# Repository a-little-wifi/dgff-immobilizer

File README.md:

# DGFF Immobilizer

A DGFF to PCIe adapter, based on my work on MXM Immobilizer (DGFF is just funny MXM)

Still extremely experimental and not anywhere near ready for use or testing  
DGFF pinouts taken from Dell Precision 7740 LA-H281P and Area51M LA-G881P boards  
The DGFF footprint's dimensions are unlikely to be accurate, it has been recreated from pixel measurements of a high-resolution image of a DGFF card. In any case they do not match the likely more accurate Framework Laptop 16"'s FXBeam footprint available elsewhere.  
This adapter is designed so far to work with Dell Precision and Alienware cards, their pinouts seem to be mostly identical but mirrored, so the Alienware one connects on the back side.  

I don't think I'll be finishing this project anytime soon, but maybe it can be a useful resource for others experimenting with DGFF

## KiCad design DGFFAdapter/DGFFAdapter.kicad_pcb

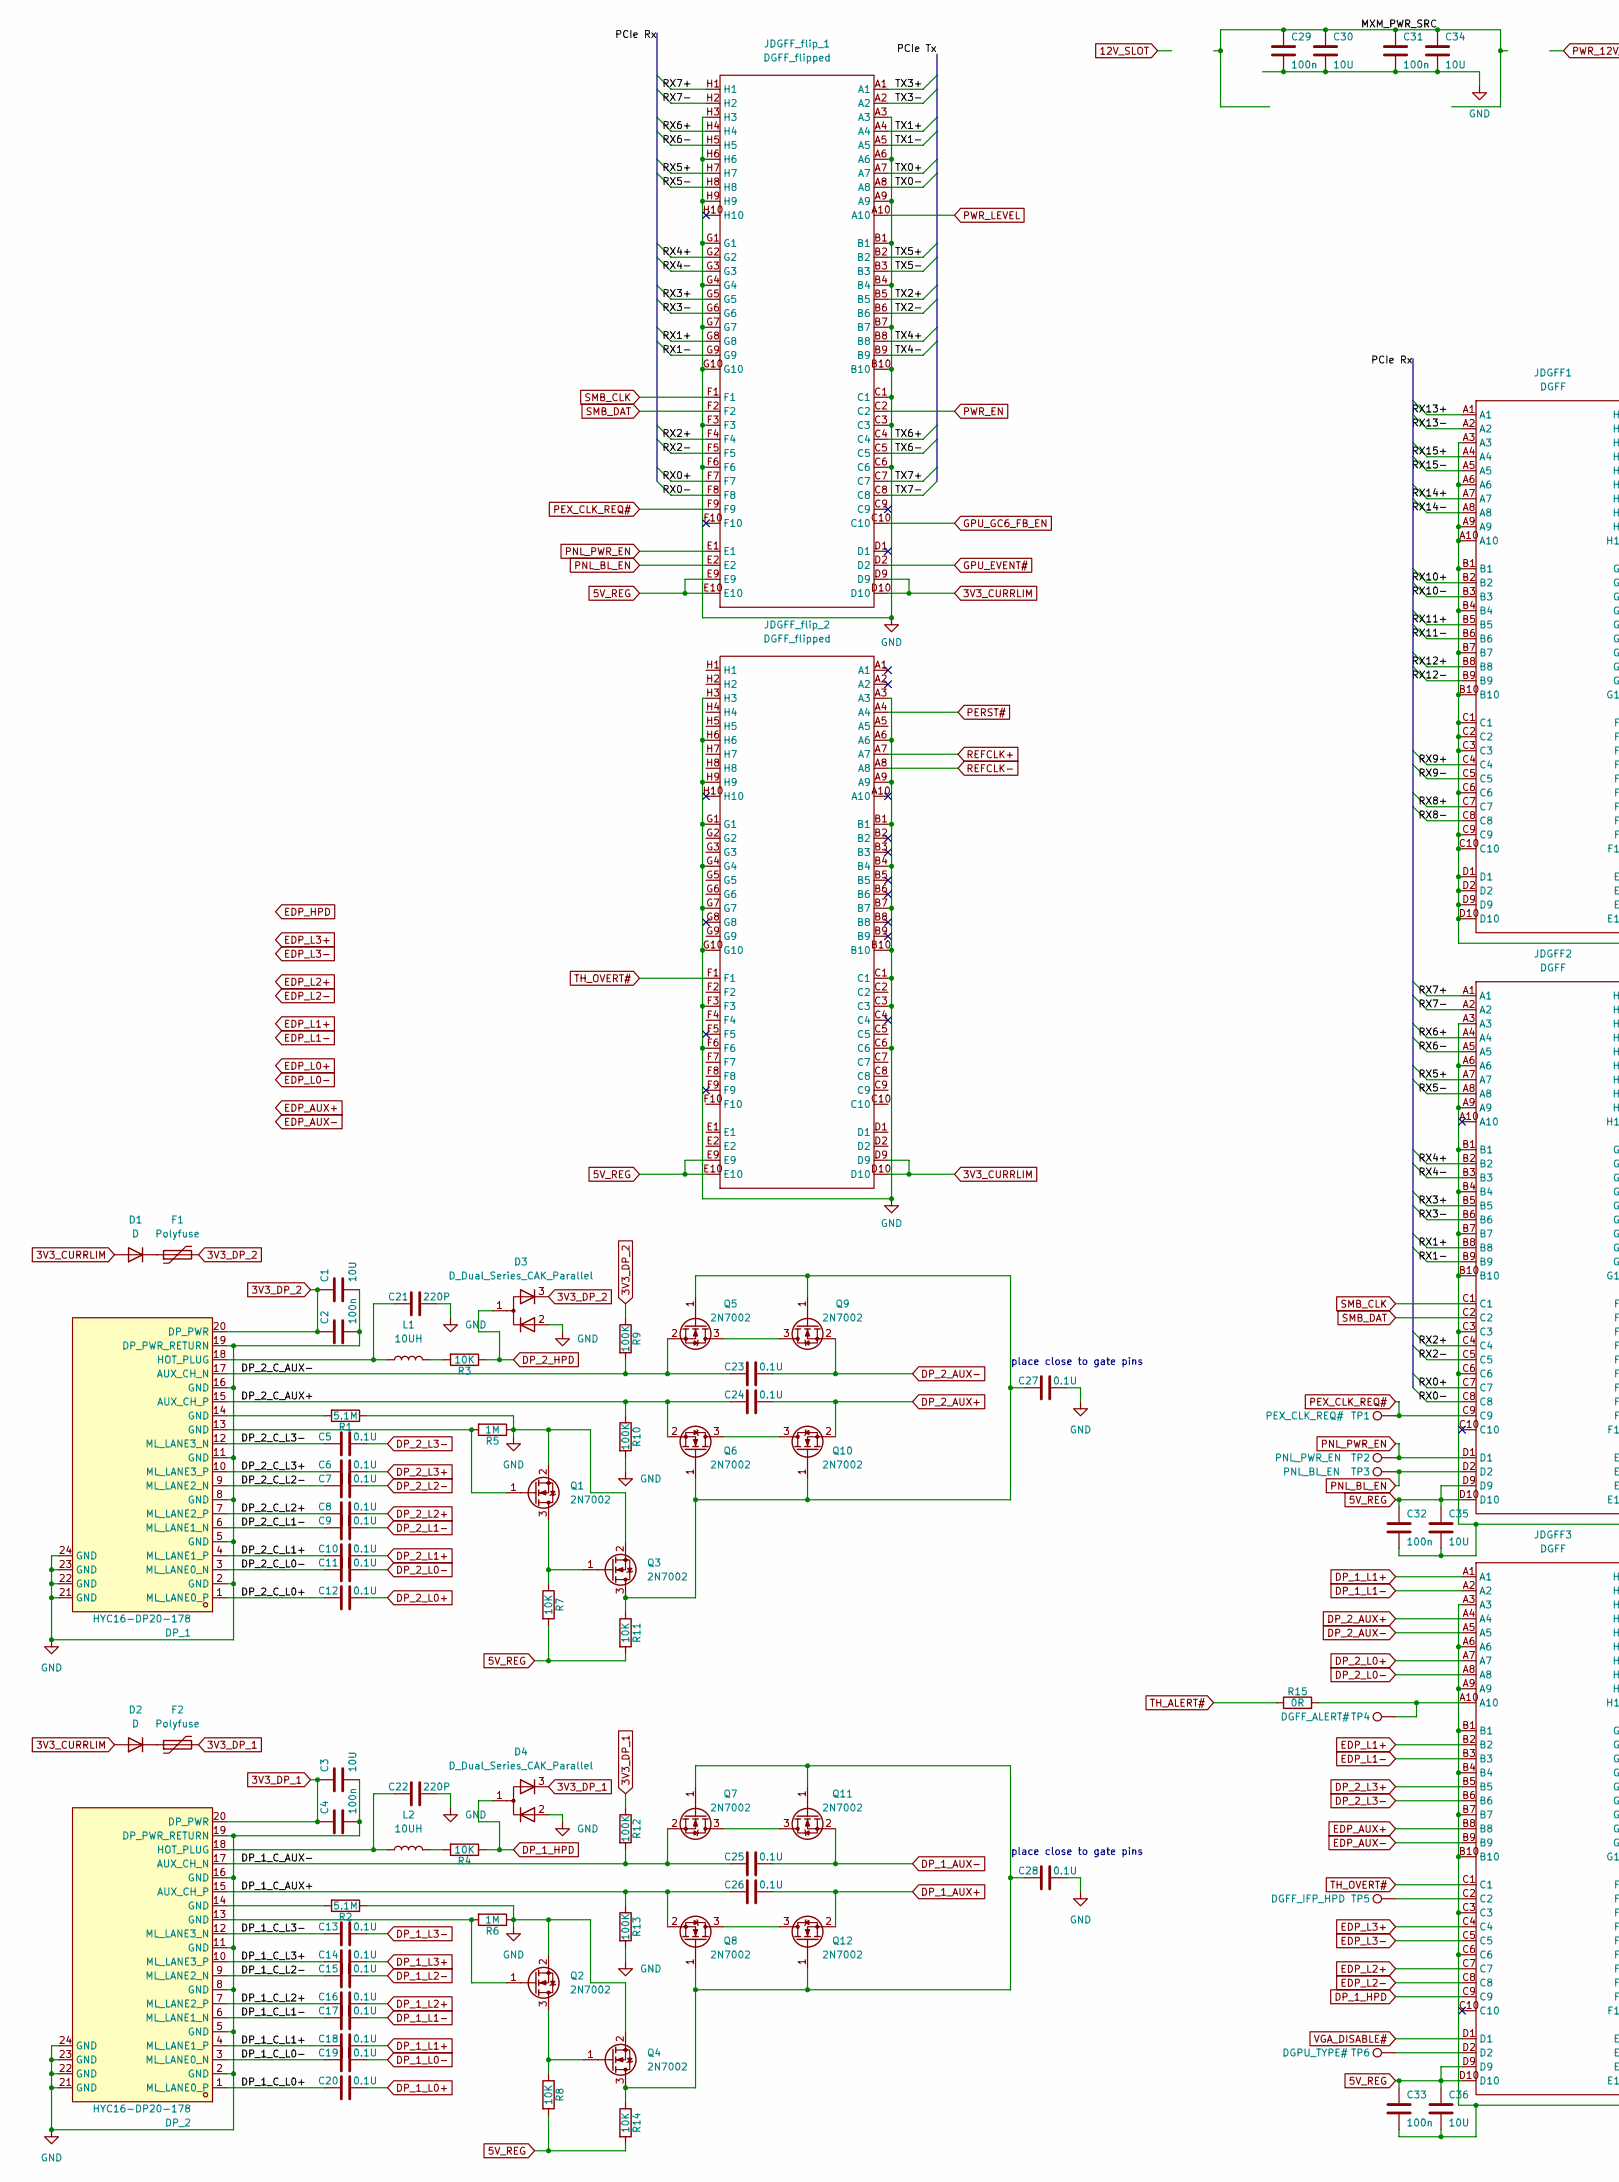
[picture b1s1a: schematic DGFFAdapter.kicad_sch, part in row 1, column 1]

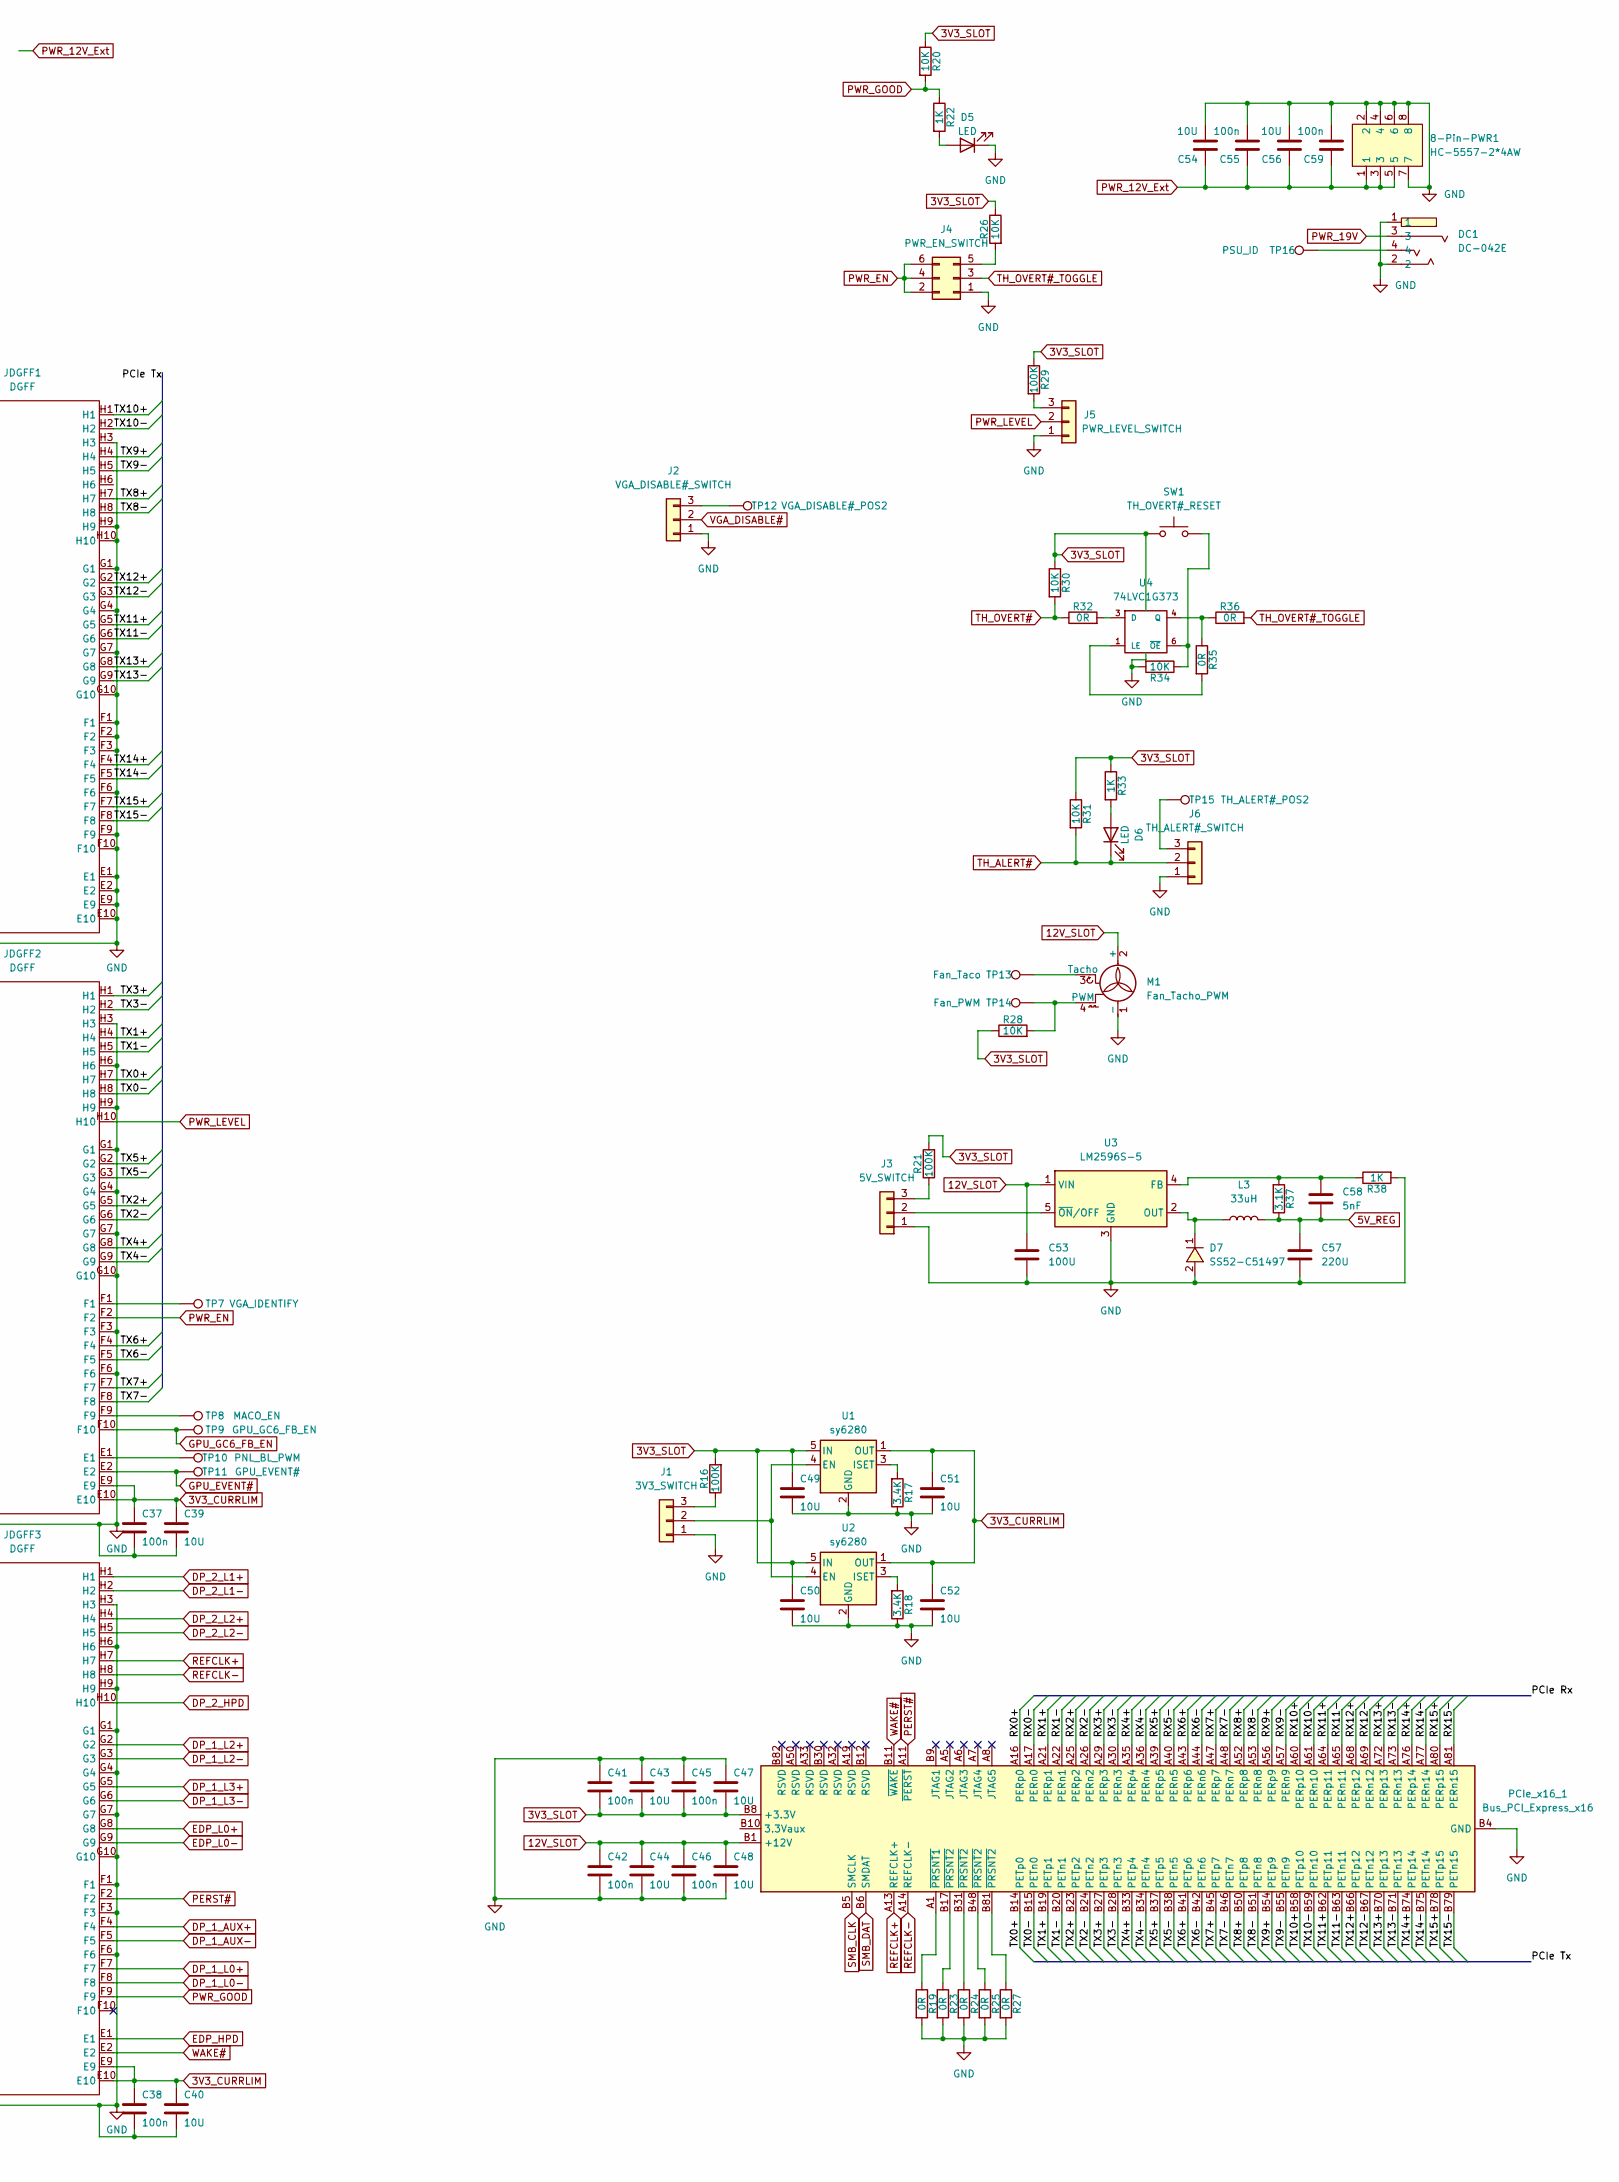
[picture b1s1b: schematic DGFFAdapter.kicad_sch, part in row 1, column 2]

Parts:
8-Pin-PWR1: HC-5557-2*4AW; CONN-TH_8P-P4.20_5557-2X4AW; LCSC Part C2845789
C1, C3, C30, C34, C35, C36, C39, C40, C43, C44, C47, C48, C49, C50, C51, C52, C54, C56: 10U; C_0603_1608Metric_Pad1.08x0.95mm_HandSolder
C2, C4, C29, C31, C32, C33, C37, C38, C41, C42, C45, C46, C55, C59: 100n; C_0603_1608Metric
C5, C6, C7, C8, C9, C10, C11, C12, C13, C14, C15, C16, C17, C18, C19, C20, C23, C24, C25, C26: 0.1U; C_0402_1005Metric
C21, C22: 220P; C_0603_1608Metric
C27, C28: 0.1U; C_0603_1608Metric
C53: 100U; C_Elec_6.3x7.7
C57: 220U; C_Elec_6.3x7.7
C58: 5nF; C_0603_1608Metric
D1, D2: D; D_SMA
D3, D4: D_Dual_Series_CAK_Parallel; SOT-23
D5, D6: LED; LED_0603_1608Metric
D7: SS52-C51497; SMB_L4.6-W3.6-LS5.3-RD; LCSC Part C51497
DC1: DC-042E; DC-IN-TH_DC-042E; LCSC Part C397340
DP_1, DP_2: HYC16-DP20-178; DP-SMD_HYC16-DP20-178; LCSC Part C711350
F1, F2: Polyfuse; Fuse_0805_2012Metric
J1: 3V3_SWITCH; PinHeader_1x03_P2.54mm_Vertical
J2: VGA_DISABLE#_SWITCH; PinHeader_1x03_P2.54mm_Vertical
J3: 5V_SWITCH; PinHeader_1x03_P2.54mm_Vertical
J4: PWR_EN_SWITCH; PinHeader_2x03_P2.54mm_Vertical
J5: PWR_LEVEL_SWITCH; PinHeader_1x03_P2.54mm_Vertical
J6: TH_ALERT#_SWITCH; PinHeader_1x03_P2.54mm_Vertical
JDGFF1, JDGFF2, JDGFF3: DGFF
JDGFF_flip_1, JDGFF_flip_2: DGFF_flipped; DGFF
L1, L2: 10UH; L_0603_1608Metric_Pad1.05x0.95mm_HandSolder
L3: 33uH; L_12x12mm_H8mm
M1: Fan_Tacho_PWM; FanPinHeader_1x04_P2.54mm_Vertical
PCIe_x16_1: Bus_PCI_Express_x16; BUS_PCIexpress_x16
Q1, Q2, Q3, Q4, Q5, Q6, Q7, Q8, Q9, Q10, Q11, Q12: 2N7002; SOT-23
R1, R2: 5.1M; R_0603_1608Metric
R3, R4, R7, R8, R11, R14, R20, R26, R28, R30, R31, R34: 10K; R_0603_1608Metric
R5, R6: 1M; R_0603_1608Metric
R9, R10, R12, R13, R16, R21, R29: 100K; R_0603_1608Metric
R15, R19, R23, R24, R25, R27, R32, R35, R36: 0R; R_0603_1608Metric
R17, R18: 3.4K; R_0603_1608Metric
R22, R33, R38: 1K; R_0603_1608Metric
R37: 3.1K; R_0603_1608Metric
SW1: TH_OVERT#_RESET; SW_SPST_EVQPE1
TP1: PEX_CLK_REQ#; PinHeader_1x01_P2.54mm_Vertical
TP2: PNL_PWR_EN; PinHeader_1x01_P2.54mm_Vertical
TP3: PNL_BL_EN; PinHeader_1x01_P2.54mm_Vertical
TP4: DGFF_ALERT#; PinHeader_1x01_P2.54mm_Vertical
TP5: DGFF_IFP_HPD; PinHeader_1x01_P2.54mm_Vertical
TP6: DGPU_TYPE#; PinHeader_1x01_P2.54mm_Vertical
TP7: VGA_IDENTIFY; PinHeader_1x01_P2.54mm_Vertical
TP8: MACO_EN; PinHeader_1x01_P2.54mm_Vertical
TP9: GPU_GC6_FB_EN; PinHeader_1x01_P2.54mm_Vertical
TP10: PNL_BL_PWM; PinHeader_1x01_P2.54mm_Vertical
TP11: GPU_EVENT#; PinHeader_1x01_P2.54mm_Vertical
TP12: VGA_DISABLE#_POS2; PinHeader_1x01_P2.54mm_Vertical
TP13: Fan_Taco; PinHeader_1x01_P2.54mm_Vertical
TP14: Fan_PWM; PinHeader_1x01_P2.54mm_Vertical
TP15: TH_ALERT#_POS2; PinHeader_1x01_P2.54mm_Vertical
TP16: PSU_ID; PinHeader_1x01_P2.54mm_Vertical
U1, U2: sy6280; SOT-23-5
U3: LM2596S-5; TO-263-5_TabPin3
U4: 74LVC1G373; SOT-23-6

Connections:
3V3_CURRLIM: C37.1, C38.1, C39.1, C40.1, C51.1, C52.1, D1.2 (A), D2.2 (A), JDGFF2.E9, JDGFF2.E10, JDGFF3.E9, JDGFF3.E10, JDGFF_flip_1.D9, JDGFF_flip_1.D10, JDGFF_flip_2.D9, JDGFF_flip_2.D10, U1.1 (OUT), U2.1 (OUT)
3V3_DP_1: C3.1, C4.1, D4.3 (K), DP_2.20 (DP_PWR), F2.2, R12.1
3V3_DP_2: C1.1, C2.1, D3.3 (K), DP_1.20 (DP_PWR), F1.2, R9.1
3V3_SLOT: C41.2, C43.2, C45.2, C47.2, C49.1, C50.1, PCIe_x16_1.A9 (+3.3V), PCIe_x16_1.A10 (+3.3V), PCIe_x16_1.B8 (+3.3V), R16.2, R20.1, R21.2, R26.1, R28.1, R29.1, R30.1, R31.1, R33.1, SW1.1, U1.5 (IN), U2.5 (IN), U4.5 (VCC)
5V_REG: C32.1, C33.1, C35.1, C36.1, C57.1, C58.2, JDGFF2.D9, JDGFF2.D10, JDGFF3.D9, JDGFF3.D10, JDGFF_flip_1.E9, JDGFF_flip_1.E10, JDGFF_flip_2.E9, JDGFF_flip_2.E10, L3.2, R7.2, R8.2, R11.2, R14.2, R37.1
12V_SLOT: C42.1, C44.1, C46.1, C48.1, C53.1, M1.2 (+), PCIe_x16_1.A2 (+12V), PCIe_x16_1.A3 (+12V), PCIe_x16_1.B1 (+12V), PCIe_x16_1.B2 (+12V), PCIe_x16_1.B3 (+12V), U3.1 (VIN)
/DP_1_C_AUX+: C26.2, DP_2.15 (AUX_CH_P), Q8.2 (S), R13.1
/DP_1_C_AUX-: C25.2, DP_2.17 (AUX_CH_N), Q7.2 (S), R12.2
/DP_1_C_L0+: C20.2, DP_2.1 (ML_LANE0_P)
/DP_1_C_L0-: C19.2, DP_2.3 (ML_LANE0_N)
/DP_1_C_L1+: C18.2, DP_2.4 (ML_LANE1_P)
/DP_1_C_L1-: C17.2, DP_2.6 (ML_LANE1_N)
/DP_1_C_L2+: C16.2, DP_2.7 (ML_LANE2_P)
/DP_1_C_L2-: C15.2, DP_2.9 (ML_LANE2_N)
/DP_1_C_L3+: C14.2, DP_2.10 (ML_LANE3_P)
/DP_1_C_L3-: C13.2, DP_2.12 (ML_LANE3_N)
/DP_2_C_AUX+: C24.2, DP_1.15 (AUX_CH_P), Q6.2 (S), R10.1
/DP_2_C_AUX-: C23.2, DP_1.17 (AUX_CH_N), Q5.2 (S), R9.2
/DP_2_C_L0+: C12.2, DP_1.1 (ML_LANE0_P)
/DP_2_C_L0-: C11.2, DP_1.3 (ML_LANE0_N)
/DP_2_C_L1+: C10.2, DP_1.4 (ML_LANE1_P)
/DP_2_C_L1-: C9.2, DP_1.6 (ML_LANE1_N)
/DP_2_C_L2+: C8.2, DP_1.7 (ML_LANE2_P)
/DP_2_C_L2-: C7.2, DP_1.9 (ML_LANE2_N)
/DP_2_C_L3+: C6.2, DP_1.10 (ML_LANE3_P)
/DP_2_C_L3-: C5.2, DP_1.12 (ML_LANE3_N)
/MXM_PWR_SRC: C29.1, C30.1, C31.1, C34.1
/RX0+: JDGFF2.C7, JDGFF_flip_1.F7, PCIe_x16_1.A16 (PERp0)
/RX0-: JDGFF2.C8, JDGFF_flip_1.F8, PCIe_x16_1.A17 (PERn0)
/RX1+: JDGFF2.B8, JDGFF_flip_1.G8, PCIe_x16_1.A21 (PERp1)
/RX1-: JDGFF2.B9, JDGFF_flip_1.G9, PCIe_x16_1.A22 (PERn1)
/RX2+: JDGFF2.C4, JDGFF_flip_1.F4, PCIe_x16_1.A25 (PERp2)
/RX2-: JDGFF2.C5, JDGFF_flip_1.F5, PCIe_x16_1.A26 (PERn2)
/RX3+: JDGFF2.B5, JDGFF_flip_1.G5, PCIe_x16_1.A29 (PERp3)
/RX3-: JDGFF2.B6, JDGFF_flip_1.G6, PCIe_x16_1.A30 (PERn3)
/RX4+: JDGFF2.B2, JDGFF_flip_1.G2, PCIe_x16_1.A35 (PERp4)
/RX4-: JDGFF2.B3, JDGFF_flip_1.G3, PCIe_x16_1.A36 (PERn4)
/RX5+: JDGFF2.A7, JDGFF_flip_1.H7, PCIe_x16_1.A39 (PERp5)
/RX5-: JDGFF2.A8, JDGFF_flip_1.H8, PCIe_x16_1.A40 (PERn5)
/RX6+: JDGFF2.A4, JDGFF_flip_1.H4, PCIe_x16_1.A43 (PERp6)
/RX6-: JDGFF2.A5, JDGFF_flip_1.H5, PCIe_x16_1.A44 (PERn6)
/RX7+: JDGFF2.A1, JDGFF_flip_1.H1, PCIe_x16_1.A47 (PERp7)
/RX7-: JDGFF2.A2, JDGFF_flip_1.H2, PCIe_x16_1.A48 (PERn7)
/RX8+: JDGFF1.C7, PCIe_x16_1.A52 (PERp8)
/RX8-: JDGFF1.C8, PCIe_x16_1.A53 (PERn8)
/RX9+: JDGFF1.C4, PCIe_x16_1.A56 (PERp9)
/RX9-: JDGFF1.C5, PCIe_x16_1.A57 (PERn9)
/RX10+: JDGFF1.B2, PCIe_x16_1.A60 (PERp10)
/RX10-: JDGFF1.B3, PCIe_x16_1.A61 (PERn10)
/RX11+: JDGFF1.B5, PCIe_x16_1.A64 (PERp11)
/RX11-: JDGFF1.B6, PCIe_x16_1.A65 (PERn11)
/RX12+: JDGFF1.B8, PCIe_x16_1.A68 (PERp12)
/RX12-: JDGFF1.B9, PCIe_x16_1.A69 (PERn12)
/RX13+: JDGFF1.A1, PCIe_x16_1.A72 (PERp13)
/RX13-: JDGFF1.A2, PCIe_x16_1.A73 (PERn13)
/RX14+: JDGFF1.A7, PCIe_x16_1.A76 (PERp14)
/RX14-: JDGFF1.A8, PCIe_x16_1.A77 (PERn14)
/RX15+: JDGFF1.A4, PCIe_x16_1.A80 (PERp15)
/RX15-: JDGFF1.A5, PCIe_x16_1.A81 (PERn15)
/TX0+: JDGFF2.H7, JDGFF_flip_1.A7, PCIe_x16_1.B14 (PETp0)
/TX0-: JDGFF2.H8, JDGFF_flip_1.A8, PCIe_x16_1.B15 (PETn0)
/TX1+: JDGFF2.H4, JDGFF_flip_1.A4, PCIe_x16_1.B19 (PETp1)
/TX1-: JDGFF2.H5, JDGFF_flip_1.A5, PCIe_x16_1.B20 (PETn1)
/TX2+: JDGFF2.G5, JDGFF_flip_1.B5, PCIe_x16_1.B23 (PETp2)
/TX2-: JDGFF2.G6, JDGFF_flip_1.B6, PCIe_x16_1.B24 (PETn2)
/TX3+: JDGFF2.H1, JDGFF_flip_1.A1, PCIe_x16_1.B27 (PETp3)
/TX3-: JDGFF2.H2, JDGFF_flip_1.A2, PCIe_x16_1.B28 (PETn3)
/TX4+: JDGFF2.G8, JDGFF_flip_1.B8, PCIe_x16_1.B33 (PETp4)
/TX4-: JDGFF2.G9, JDGFF_flip_1.B9, PCIe_x16_1.B34 (PETn4)
/TX5+: JDGFF2.G2, JDGFF_flip_1.B2, PCIe_x16_1.B37 (PETp5)
/TX5-: JDGFF2.G3, JDGFF_flip_1.B3, PCIe_x16_1.B38 (PETn5)
/TX6+: JDGFF2.F4, JDGFF_flip_1.C4, PCIe_x16_1.B41 (PETp6)
/TX6-: JDGFF2.F5, JDGFF_flip_1.C5, PCIe_x16_1.B42 (PETn6)
/TX7+: JDGFF2.F7, JDGFF_flip_1.C7, PCIe_x16_1.B45 (PETp7)
/TX7-: JDGFF2.F8, JDGFF_flip_1.C8, PCIe_x16_1.B46 (PETn7)
/TX8+: JDGFF1.H7, PCIe_x16_1.B50 (PETp8)
/TX8-: JDGFF1.H8, PCIe_x16_1.B51 (PETn8)
/TX9+: JDGFF1.H4, PCIe_x16_1.B54 (PETp9)
/TX9-: JDGFF1.H5, PCIe_x16_1.B55 (PETn9)
/TX10+: JDGFF1.H1, PCIe_x16_1.B58 (PETp10)
/TX10-: JDGFF1.H2, PCIe_x16_1.B59 (PETn10)
/TX11+: JDGFF1.G5, PCIe_x16_1.B62 (PETp11)
/TX11-: JDGFF1.G6, PCIe_x16_1.B63 (PETn11)
/TX12+: JDGFF1.G2, PCIe_x16_1.B66 (PETp12)
/TX12-: JDGFF1.G3, PCIe_x16_1.B67 (PETn12)
/TX13+: JDGFF1.G8, PCIe_x16_1.B70 (PETp13)
/TX13-: JDGFF1.G9, PCIe_x16_1.B71 (PETn13)
/TX14+: JDGFF1.F4, PCIe_x16_1.B74 (PETp14)
/TX14-: JDGFF1.F5, PCIe_x16_1.B75 (PETn14)
/TX15+: JDGFF1.F7, PCIe_x16_1.B78 (PETp15)
/TX15-: JDGFF1.F8, PCIe_x16_1.B79 (PETn15)
DP_1_AUX+: C26.1, JDGFF3.F4, Q12.2 (S)
DP_1_AUX-: C25.1, JDGFF3.F5, Q11.2 (S)
DP_1_HPD: D4.1 (A), JDGFF3.C9, R4.1
DP_1_L0+: C20.1, JDGFF3.F7
DP_1_L0-: C19.1, JDGFF3.F8
DP_1_L1+: C18.1, JDGFF3.A1
DP_1_L1-: C17.1, JDGFF3.A2
DP_1_L2+: C16.1, JDGFF3.G2
DP_1_L2-: C15.1, JDGFF3.G3
DP_1_L3+: C14.1, JDGFF3.G5
DP_1_L3-: C13.1, JDGFF3.G6
DP_2_AUX+: C24.1, JDGFF3.A4, Q10.2 (S)
DP_2_AUX-: C23.1, JDGFF3.A5, Q9.2 (S)
DP_2_HPD: D3.1 (A), JDGFF3.H10, R3.1
DP_2_L0+: C12.1, JDGFF3.A7
DP_2_L0-: C11.1, JDGFF3.A8
DP_2_L1+: C10.1, JDGFF3.H1
DP_2_L1-: C9.1, JDGFF3.H2
DP_2_L2+: C8.1, JDGFF3.H4
DP_2_L2-: C7.1, JDGFF3.H5
DP_2_L3+: C6.1, JDGFF3.B5
DP_2_L3-: C5.1, JDGFF3.B6
EDP_AUX+: JDGFF3.B8
EDP_AUX-: JDGFF3.B9
EDP_HPD: JDGFF3.E1
EDP_L0+: JDGFF3.G8
EDP_L0-: JDGFF3.G9
EDP_L1+: JDGFF3.B2
EDP_L1-: JDGFF3.B3
EDP_L2+: JDGFF3.C7
EDP_L2-: JDGFF3.C8
EDP_L3+: JDGFF3.C4
EDP_L3-: JDGFF3.C5
GND: 8-Pin-PWR1.2, 8-Pin-PWR1.4, 8-Pin-PWR1.6, 8-Pin-PWR1.7, 8-Pin-PWR1.8, C1.2, C2.2, C3.2, C4.2, C21.1, C22.1, C27.1, C28.1, C29.2, C30.2, C31.2, C32.2, C33.2, C34.2, C35.2, C36.2, C37.2, C38.2, C39.2, C40.2, C41.1, C42.2, C43.1, C44.2, C45.1, C46.2, C47.1, C48.2, C49.2, C50.2, C51.2, C52.2, C53.2, C54.2, C55.2, C56.2, C57.2, C59.2, D3.2 (K), D4.2 (K), D5.1 (K), D7.2 (A), DC1.1, DC1.2, DP_1.2 (GND), DP_1.5 (GND), DP_1.8 (GND), DP_1.11 (GND), DP_1.16 (GND), DP_1.19 (DP_PWR_RETURN), DP_1.21 (GND), DP_1.22 (GND), DP_1.23 (GND), DP_1.24 (GND), DP_2.2 (GND), DP_2.5 (GND), DP_2.8 (GND), DP_2.11 (GND), DP_2.16 (GND), DP_2.19 (DP_PWR_RETURN), DP_2.21 (GND), DP_2.22 (GND), DP_2.23 (GND), DP_2.24 (GND), J1.1, J2.1, J3.1, J4.1, J5.1, J6.1, JDGFF1.A3, JDGFF1.A6, JDGFF1.A9, JDGFF1.A10, JDGFF1.B1, JDGFF1.B4, JDGFF1.B7, JDGFF1.B10, JDGFF1.C1, JDGFF1.C2, JDGFF1.C3, JDGFF1.C6, JDGFF1.C9, JDGFF1.C10, JDGFF1.D1, JDGFF1.D2, JDGFF1.D9, JDGFF1.D10, JDGFF1.E1, JDGFF1.E2, JDGFF1.E9, JDGFF1.E10, JDGFF1.F1, JDGFF1.F2, JDGFF1.F3, JDGFF1.F6, JDGFF1.F9, JDGFF1.F10, JDGFF1.G1, JDGFF1.G4, JDGFF1.G7, JDGFF1.G10, JDGFF1.H3, JDGFF1.H9, JDGFF1.H10, JDGFF2.A3, JDGFF2.A6, JDGFF2.A9, JDGFF2.B1, JDGFF2.B4, JDGFF2.B7, JDGFF2.B10, JDGFF2.C3, JDGFF2.C6, JDGFF2.F3, JDGFF2.F6, JDGFF2.G1, JDGFF2.G4, JDGFF2.G7, JDGFF2.G10, JDGFF2.H3, JDGFF2.H6, JDGFF2.H9, JDGFF3.A3, JDGFF3.A6, JDGFF3.A9, JDGFF3.B1, JDGFF3.B4, JDGFF3.B7, JDGFF3.B10, JDGFF3.C3, JDGFF3.C6, JDGFF3.F1, JDGFF3.F3, JDGFF3.F6, JDGFF3.G1, JDGFF3.G4, JDGFF3.G7, JDGFF3.G10, JDGFF3.H3, JDGFF3.H6, JDGFF3.H9, JDGFF_flip_1.A3, JDGFF_flip_1.A6, JDGFF_flip_1.A9, JDGFF_flip_1.B1, JDGFF_flip_1.B4, JDGFF_flip_1.B7, JDGFF_flip_1.B10, JDGFF_flip_1.C1, JDGFF_flip_1.C3, JDGFF_flip_1.C6, JDGFF_flip_1.F3, JDGFF_flip_1.F6, JDGFF_flip_1.G1, JDGFF_flip_1.G4, JDGFF_flip_1.G7, JDGFF_flip_1.G10, JDGFF_flip_1.H3, JDGFF_flip_1.H6, JDGFF_flip_1.H9, JDGFF_flip_2.A3, JDGFF_flip_2.A6, JDGFF_flip_2.A9, JDGFF_flip_2.B1, JDGFF_flip_2.B4, JDGFF_flip_2.B7, JDGFF_flip_2.B10, JDGFF_flip_2.C1, JDGFF_flip_2.C3, JDGFF_flip_2.C6, JDGFF_flip_2.F3, JDGFF_flip_2.F6, JDGFF_flip_2.G1, JDGFF_flip_2.G4, JDGFF_flip_2.G7, JDGFF_flip_2.G10, JDGFF_flip_2.H3, JDGFF_flip_2.H6, JDGFF_flip_2.H9, M1.1 (-), PCIe_x16_1.A4 (GND), PCIe_x16_1.A12 (GND), PCIe_x16_1.A15 (GND), PCIe_x16_1.A18 (GND), PCIe_x16_1.A20 (GND), PCIe_x16_1.A23 (GND), PCIe_x16_1.A24 (GND), PCIe_x16_1.A27 (GND), PCIe_x16_1.A28 (GND), PCIe_x16_1.A31 (GND), PCIe_x16_1.A34 (GND), PCIe_x16_1.A37 (GND), PCIe_x16_1.A38 (GND), PCIe_x16_1.A41 (GND), PCIe_x16_1.A42 (GND), PCIe_x16_1.A45 (GND), PCIe_x16_1.A46 (GND), PCIe_x16_1.A49 (GND), PCIe_x16_1.A51 (GND), PCIe_x16_1.A54 (GND), PCIe_x16_1.A55 (GND), PCIe_x16_1.A58 (GND), PCIe_x16_1.A59 (GND), PCIe_x16_1.A62 (GND), PCIe_x16_1.A63 (GND), PCIe_x16_1.A66 (GND), PCIe_x16_1.A67 (GND), PCIe_x16_1.A70 (GND), PCIe_x16_1.A71 (GND), PCIe_x16_1.A74 (GND), PCIe_x16_1.A75 (GND), PCIe_x16_1.A78 (GND), PCIe_x16_1.A79 (GND), PCIe_x16_1.A82 (GND), PCIe_x16_1.B4 (GND), PCIe_x16_1.B7 (GND), PCIe_x16_1.B13 (GND), PCIe_x16_1.B16 (GND), PCIe_x16_1.B18 (GND), PCIe_x16_1.B21 (GND), PCIe_x16_1.B22 (GND), PCIe_x16_1.B25 (GND), PCIe_x16_1.B26 (GND), PCIe_x16_1.B29 (GND), PCIe_x16_1.B32 (GND), PCIe_x16_1.B35 (GND), PCIe_x16_1.B36 (GND), PCIe_x16_1.B39 (GND), PCIe_x16_1.B40 (GND), PCIe_x16_1.B43 (GND), PCIe_x16_1.B44 (GND), PCIe_x16_1.B47 (GND), PCIe_x16_1.B49 (GND), PCIe_x16_1.B52 (GND), PCIe_x16_1.B53 (GND), PCIe_x16_1.B56 (GND), PCIe_x16_1.B57 (GND), PCIe_x16_1.B60 (GND), PCIe_x16_1.B61 (GND), PCIe_x16_1.B64 (GND), PCIe_x16_1.B65 (GND), PCIe_x16_1.B68 (GND), PCIe_x16_1.B69 (GND), PCIe_x16_1.B72 (GND), PCIe_x16_1.B73 (GND), PCIe_x16_1.B76 (GND), PCIe_x16_1.B77 (GND), PCIe_x16_1.B80 (GND), Q1.2 (S), Q2.2 (S), Q3.2 (S), Q4.2 (S), R1.1, R2.1, R5.1, R6.1, R10.2, R13.2, R17.1, R18.1, R19.2, R23.2, R24.2, R25.2, R27.2, R34.2, R38.2, U1.2 (GND), U2.2 (GND), U3.3 (GND), U4.2 (GND)
GPU_EVENT#: JDGFF2.E2, JDGFF_flip_1.D2, TP11.1
GPU_GC6_FB_EN: JDGFF2.F10, JDGFF_flip_1.C10, TP9.1
unnamed: D1.1 (K), F1.1
unnamed: D2.1 (K), F2.1
unnamed: D5.2 (A), R22.2
unnamed: D6.2 (A), R33.2
unnamed: D7.1 (C), L3.1, U3.2 (OUT)
unnamed: DC1.4, TP16.1
unnamed: DP_1.14 (GND), R1.2
unnamed: C21.2, DP_1.18 (HOT_PLUG), L1.1
unnamed: DP_2.14 (GND), R2.2
unnamed: C22.2, DP_2.18 (HOT_PLUG), L2.1
unnamed: J1.2, U1.4 (EN), U2.4 (EN)
unnamed: J1.3, R16.1
unnamed: J2.3, TP12.1
unnamed: J3.2, U3.5 (~ON/OFF)
unnamed: J3.3, R21.1
unnamed: J4.5, R26.2
unnamed: J5.3, R29.2
unnamed: J6.3, TP15.1
unnamed: JDGFF2.E1, TP10.1
unnamed: JDGFF2.F1, TP7.1
unnamed: JDGFF2.F9, TP8.1
unnamed: JDGFF3.A10, R15.2, TP4.1
unnamed: JDGFF3.C2, TP5.1
unnamed: JDGFF3.D2, TP6.1
unnamed: L1.2, R3.2
unnamed: L2.2, R4.2
unnamed: M1.4 (PWM), R28.2, TP14.1
unnamed: M1.3 (Tacho), TP13.1
unnamed: PCIe_x16_1.A1 (~PRSNT1), R19.1
unnamed: PCIe_x16_1.B17 (~PRSNT2), R23.1
unnamed: PCIe_x16_1.B31 (~PRSNT2), R24.1
unnamed: PCIe_x16_1.B48 (~PRSNT2), R25.1
unnamed: PCIe_x16_1.B81 (~PRSNT2), R27.1
unnamed: Q1.3 (D), Q3.1 (G), R7.1
unnamed: DP_1.13 (GND), Q1.1 (G), R5.2
unnamed: Q2.3 (D), Q4.1 (G), R8.1
unnamed: DP_2.13 (GND), Q2.1 (G), R6.2
unnamed: Q5.3 (D), Q9.3 (D)
unnamed: Q6.3 (D), Q10.3 (D)
unnamed: C27.2, Q3.3 (D), Q5.1 (G), Q6.1 (G), Q9.1 (G), Q10.1 (G), R11.1
unnamed: Q7.3 (D), Q11.3 (D)
unnamed: C28.2, Q4.3 (D), Q7.1 (G), Q8.1 (G), Q11.1 (G), Q12.1 (G), R14.1
unnamed: Q8.3 (D), Q12.3 (D)
unnamed: R17.2, U1.3 (ISET)
unnamed: R18.2, U2.3 (ISET)
unnamed: C58.1, R37.2, R38.1, U3.4 (FB)
unnamed: R32.2, U4.3 (D)
unnamed: R35.2, U4.1 (LE)
unnamed: R35.1, R36.1, U4.4 (Q)
unnamed: R34.1, SW1.2, U4.6 (~OE)
PERST#: JDGFF3.F2, JDGFF_flip_2.A4, PCIe_x16_1.A11 (~PERST)
PEX_CLK_REQ#: JDGFF2.C9, JDGFF_flip_1.F9, TP1.1
PNL_BL_EN: JDGFF2.D2, JDGFF_flip_1.E2, TP3.1
PNL_PWR_EN: JDGFF2.D1, JDGFF_flip_1.E1, TP2.1
PWR_12V_Ext: 8-Pin-PWR1.1, 8-Pin-PWR1.3, 8-Pin-PWR1.5, C54.1, C55.1, C56.1, C59.1
PWR_19V: DC1.3
PWR_EN: J4.2, J4.4, J4.6, JDGFF2.F2, JDGFF_flip_1.C2
PWR_GOOD: JDGFF3.F9, R20.2, R22.1
PWR_LEVEL: J5.2, JDGFF2.H10, JDGFF_flip_1.A10
REFCLK+: JDGFF3.H7, JDGFF_flip_2.A7, PCIe_x16_1.A13 (REFCLK+)
REFCLK-: JDGFF3.H8, JDGFF_flip_2.A8, PCIe_x16_1.A14 (REFCLK-)
SMB_CLK: JDGFF2.C1, JDGFF_flip_1.F1, PCIe_x16_1.B5 (SMCLK)
SMB_DAT: JDGFF2.C2, JDGFF_flip_1.F2, PCIe_x16_1.B6 (SMDAT)
TH_ALERT#: D6.1 (K), J6.2, R15.1, R31.2
TH_OVERT#: JDGFF3.C1, JDGFF_flip_2.F1, R30.2, R32.1
TH_OVERT#_TOGGLE: J4.3, R36.2
VGA_DISABLE#: J2.2, JDGFF3.D1
WAKE#: JDGFF3.E2, PCIe_x16_1.B11 (~WAKE)

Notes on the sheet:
place close to gate pins

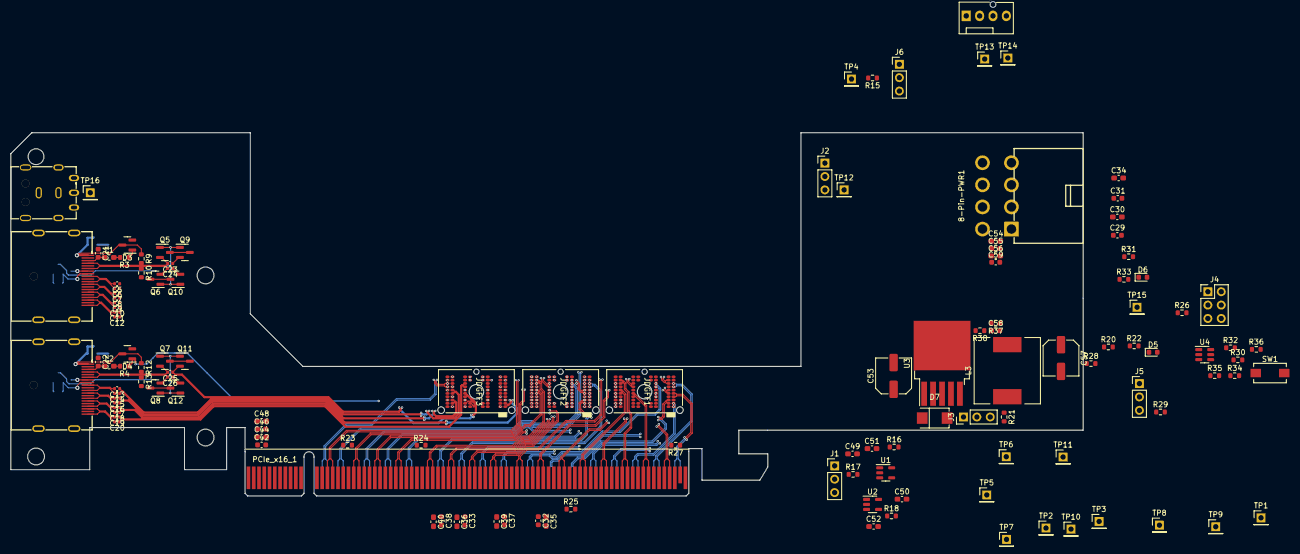
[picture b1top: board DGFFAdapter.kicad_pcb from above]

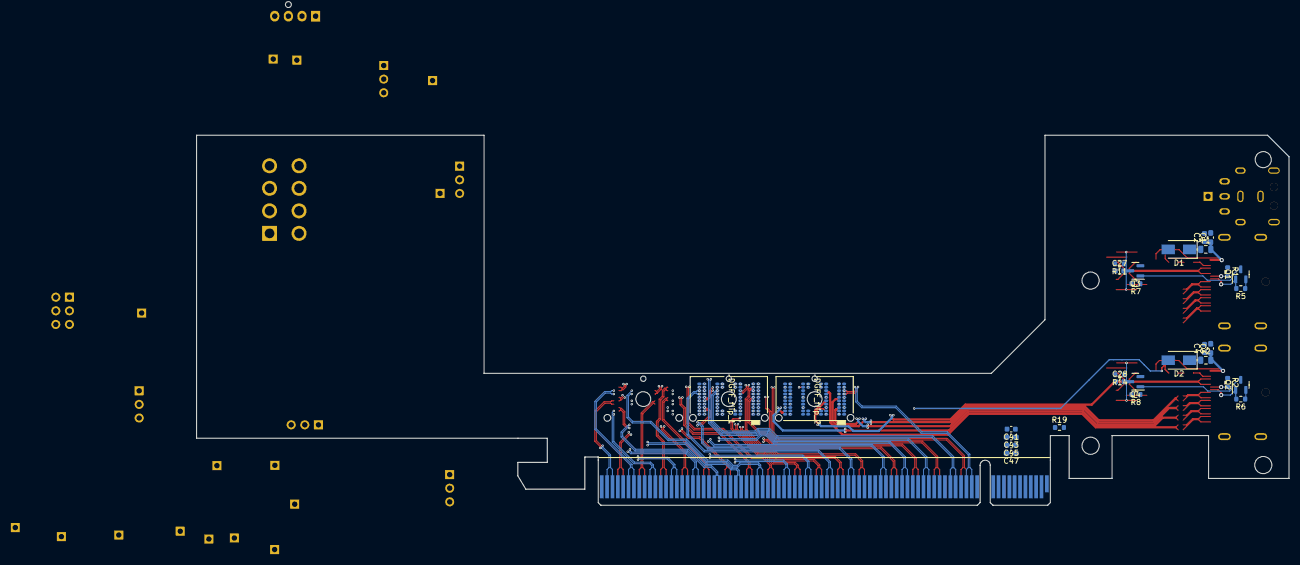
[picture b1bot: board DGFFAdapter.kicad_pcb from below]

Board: 6 copper layers, 203.7 x 69.0 mm, 159 parts (29 on the bottom side), 183 nets.

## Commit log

2024-09-26 Added files and readme
2024-09-26 Slight readme picture adjustment
2024-09-26 Added pixel measurement photos
